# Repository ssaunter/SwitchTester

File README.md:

# SwitchTester
 
 SwitchTester is a 5-key switch PCB and housing to test the feel of different Cherry MX switches. Addressable LEDs have two modes: always on (colored), and fade when pressed.

# The PCB

The PCB follows a similar architecture to the Hackpad, and upgrades with decoupling capacitors and a switch to control LED modes. The code is set up to adjust the LED modes depending on the slide switch mode.

# Assembly

The lower and upper case sections are to be 3D printed. The device is assembled using 2x M3x5x5 heatset inserts and 2x M3x10 bolts. The PCB is aligned in the lower case, and the top case encloses it before being bolted down through the standoffs. It should be stable enough, but the USB-C recepticle also nicely rests into the opposite side for added stability. If I find that it is unstable even then, I can add standoffs without holes thoughout the lower case.

# Firmware

The code was created in the Arduino IDE, and uses the FastLED library for the SMD LEDs. The colors are based on guesses, and I will change the code after testing the values.

The first section of the code is simply setup and definitions. It sets the switches as inputs and assigns the pullup resistors, and also initializes the LED index.

The main loop determines the current LED_MODE, checks for keyswitch presses, and outputs to the LED based on the mode and user interaction. FastLED.show() is used to queue the LED instructions and send data through the LED_DATA line.

# BOM

| Part | Quantity | Price Per | Link | 
| :--- | :---: | :---: | :--- |
| **Seeduino Xiao** | 1 | $4.68 | [DigiKey](https://www.digikey.com/short/d3zzwm59) |
| **Slide Switch** | 1 | $0.65 | [DigiKey](https://www.digikey.com/short/p00mmw27) |  
| **0.1uF C 0603** | 5 | $0.08 | [DigiKey](https://www.digikey.com/short/3rn2v9pz) |
| **330ohm R 0603** | 1 | $0.10 | [DigiKey](https://www.digikey.com/short/2qztp77r) |
| **Neopixel LED 10pcs** | 1 | $2.95 | [DigiKey](https://www.digikey.com/short/n79w9mvw) |
| **Cherry MX Blue 60g** | 1 | $0.38 | [MechanicalKeyboards](https://mechanicalkeyboards.com/products/cherry-mx-blue-60g-clicky?variant=48007305003308) |
| **Cherry MX2A Red** | 1 | $0.38 | [MechanicalKeyboards](https://mechanicalkeyboards.com/products/cherry-mx2a-red-45g-linear?variant=48020634239276) |
| **Cherry MX2A Black** | 1 | $0.38 | [MechanicalKeyboards](https://mechanicalkeyboards.com/products/cherry-mx2a-black-60g-linear?variant=48014721253676) |
| **Cherry MX2A Brown** | 1 | $0.38 | [MechanicalKeyboards](https://mechanicalkeyboards.com/products/cherry-mx2a-brown-55g-tactile?variant=48020838383916) |
| **Cherry MX Blue 60g** | 1 | $0.38 | [MechanicalKeyboards](https://mechanicalkeyboards.com/products/cherry-mx-blue-60g-clicky?variant=48007305003308) |
| **DSA Keycaps** | 5 | (have) |  |
| **1x7 Male Headers** | 2 | (have) |  |
| **M3x5x5 Heatset Inserts** | 2 | (have) |  |
| **M3x10 Bolt** | 2 | (have) |  |

Totals
---
| Service  | Price | 
| :--- | :--- |
| **JLCPCB Order** |  $8.52 | 
| **DigiKey Order** |  $16.92 | 
| **MechanicalKeyboards Order** |  $12.54 | 
| **GRAND TOTAL:** |  $37.98 | 

Orders: 
---

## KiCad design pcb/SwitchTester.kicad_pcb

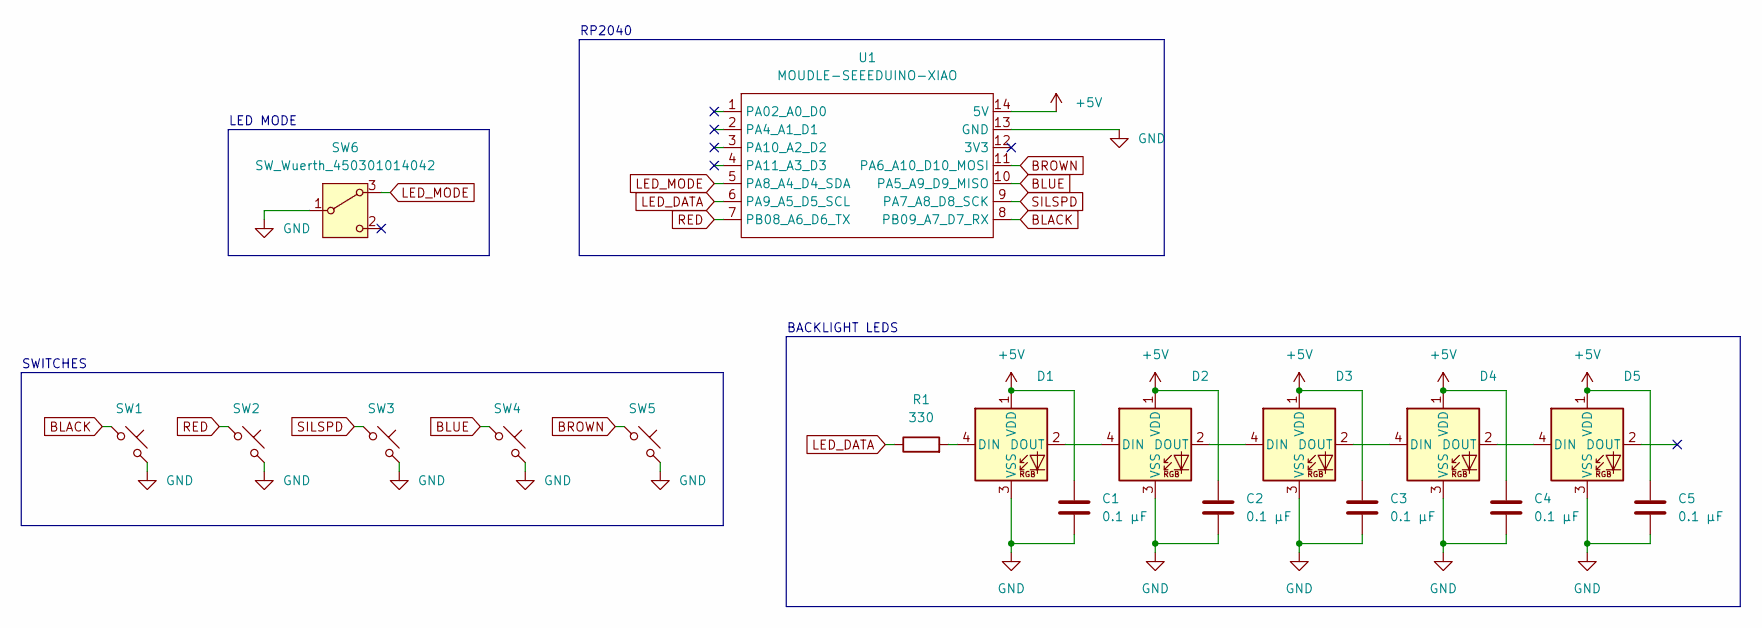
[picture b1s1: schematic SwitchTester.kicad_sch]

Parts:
C1, C2, C3, C4, C5: 0.1 μF; C_0603_1608Metric
D1, D2, D3, D4, D5: SK6812MINI-E; SK6812MINI-E_fixed
R1: 330; R_0603_1608Metric
SW1, SW2, SW3, SW4, SW5: SW_Push_45deg; SW_Cherry_MX_1.00u_PCB
SW6: SW_Wuerth_450301014042; SW_Slide_SPDT_Angled_CK_OS102011MA1Q
U1: MOUDLE-SEEEDUINO-XIAO; XIAO-Generic-Hybrid-14P-2.54-21X17.8MM

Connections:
+5V: C1.1, C2.1, C3.1, C4.1, C5.1, D1.1 (VDD), D2.1 (VDD), D3.1 (VDD), D4.1 (VDD), D5.1 (VDD), U1.14 (5V)
BLACK: SW1.1, U1.8 (PB09_A7_D7_RX)
BLUE: SW4.1, U1.10 (PA5_A9_D9_MISO)
BROWN: SW5.1, U1.11 (PA6_A10_D10_MOSI)
GND: C1.2, C2.2, C3.2, C4.2, C5.2, D1.3 (VSS), D2.3 (VSS), D3.3 (VSS), D4.3 (VSS), D5.3 (VSS), SW1.2, SW2.2, SW3.2, SW4.2, SW5.2, SW6.1 (B), U1.13 (GND)
LED_DATA: R1.1, U1.6 (PA9_A5_D5_SCL)
LED_MODE: SW6.3 (A), U1.5 (PA8_A4_D4_SDA)
unnamed: D1.4 (DIN), R1.2
unnamed: D1.2 (DOUT), D2.4 (DIN)
unnamed: D2.2 (DOUT), D3.4 (DIN)
unnamed: D3.2 (DOUT), D4.4 (DIN)
unnamed: D4.2 (DOUT), D5.4 (DIN)
RED: SW2.1, U1.7 (PB08_A6_D6_TX)
SILSPD: SW3.1, U1.9 (PA7_A8_D8_SCK)

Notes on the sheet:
RP2040
LED MODE
SWITCHES
BACKLIGHT LEDS

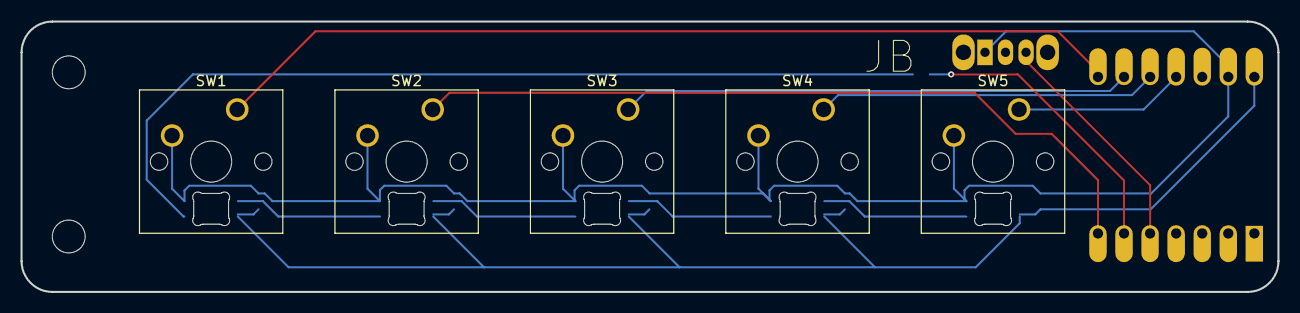
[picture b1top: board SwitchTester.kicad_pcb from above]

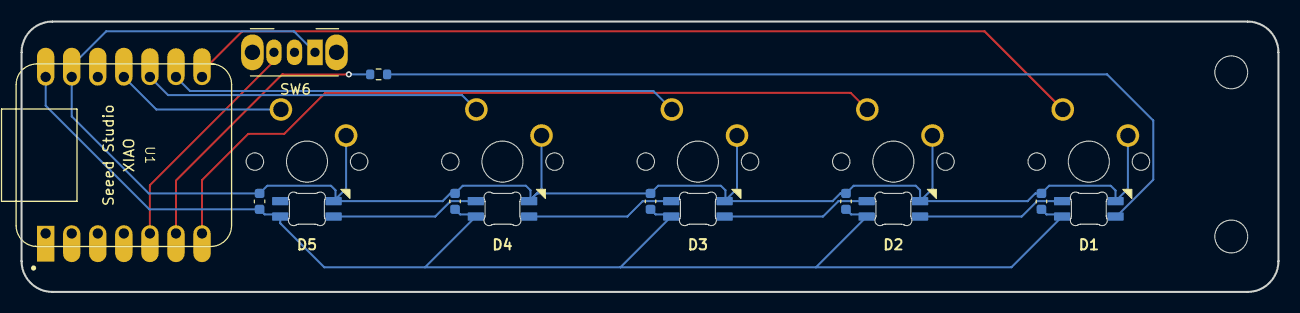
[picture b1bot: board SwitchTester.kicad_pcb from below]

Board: 2 copper layers, 122.5 x 26.3 mm, 18 parts (8 on the bottom side), 14 nets.

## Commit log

2026-04-01 main commit
2026-04-01 added hardware to bom
2026-04-27 uploaded f3z file
